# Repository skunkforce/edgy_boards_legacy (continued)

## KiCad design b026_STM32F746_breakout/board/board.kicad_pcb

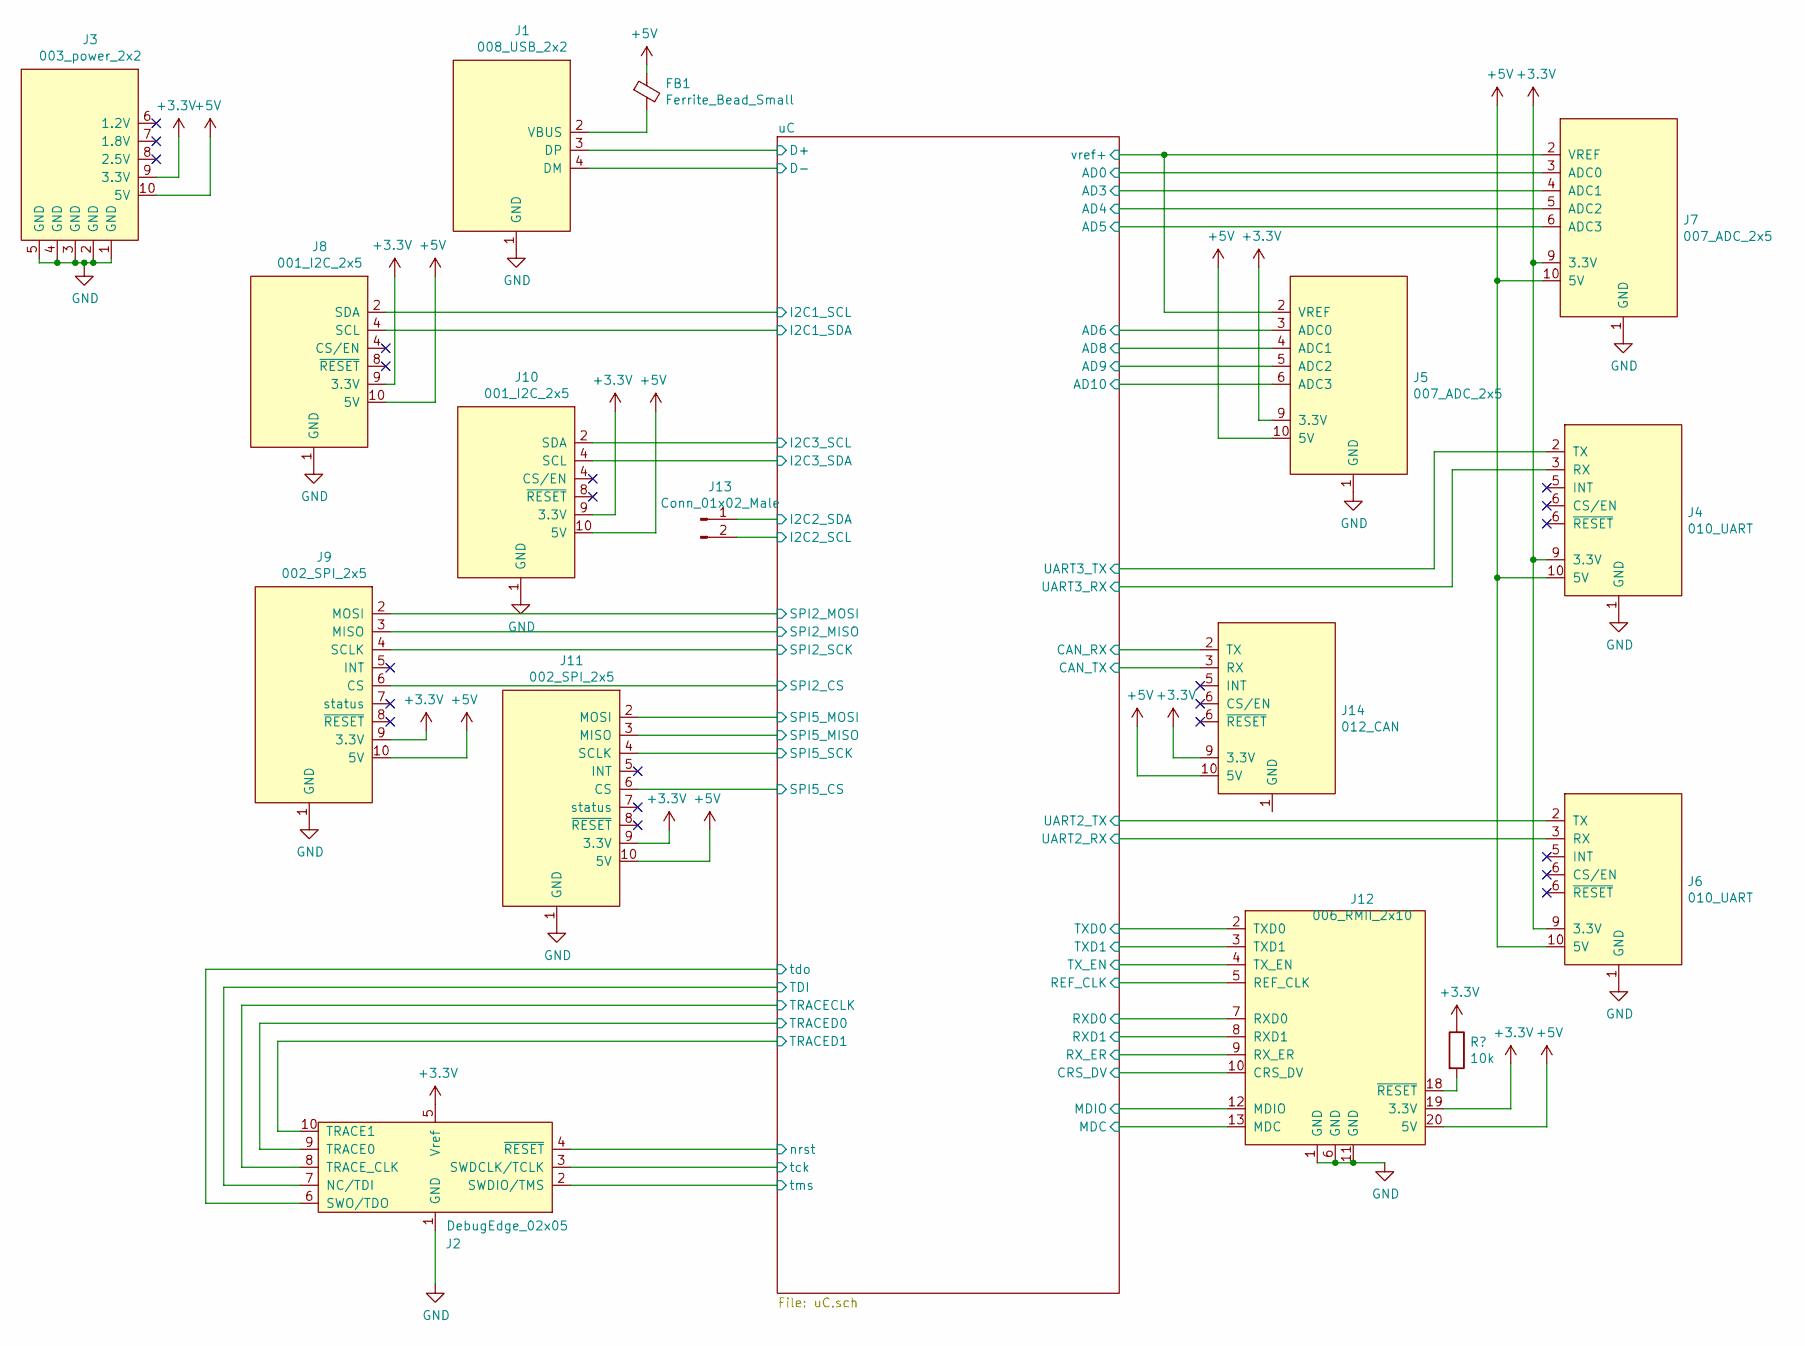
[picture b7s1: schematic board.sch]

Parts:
FB1: Ferrite_Bead_Small; L_0805_2012Metric
J1: 008_USB_2x2; on_edge_2x05_device
J2: DebugEdge_02x05; on_edge_2x05_device
J3: 003_power_2x2; on_edge_2x05_device
J4: 010_UART; on_edge_2x05_device
J5, J7: 007_ADC_2x5; on_edge_2x05_host
J6: 010_UART; on_edge_2x05_up_host
J8, J10: 001_I2C_2x5; on_edge_2x05_up_host
J9, J11: 002_SPI_2x5; on_edge_2x05_up_host
J12: 006_RMII_2x10; on_edge_2x10_host
J13: Conn_01x02_Male; PinHeader_1x02_P2.00mm_Vertical
J14: 012_CAN; on_edge_2x05_up_host

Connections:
+5V: FB1.1, J3.10 (5V), J4.10 (5V), J5.10 (5V), J6.10 (5V), J7.10 (5V), J8.10 (5V), J9.10 (5V), J10.10 (5V), J11.10 (5V), J12.20 (5V), J14.10 (5V)
/uC/AD0: J7.3 (ADC0); also elsewhere on the board
/uC/AD3: J7.4 (ADC1); also elsewhere on the board
/uC/AD4: J7.5 (ADC2); also elsewhere on the board
/uC/AD5: J7.6 (ADC3); also elsewhere on the board
/uC/AD6: J5.3 (ADC0); also elsewhere on the board
/uC/AD8: J5.4 (ADC1); also elsewhere on the board
/uC/AD9: J5.5 (ADC2); also elsewhere on the board
/uC/AD10: J5.6 (ADC3); also elsewhere on the board
/uC/CAN_RX: J14.2 (TX); also elsewhere on the board
/uC/CAN_TX: J14.3 (RX); also elsewhere on the board
/uC/CRS_DV: J12.10 (CRS_DV); also elsewhere on the board
/uC/D+: J1.3 (DP); also elsewhere on the board
/uC/D-: J1.4 (DM); also elsewhere on the board
/uC/I2C1_SCL: J8.2 (SDA); also elsewhere on the board
/uC/I2C2_SCL: J13.2; also elsewhere on the board
/uC/I2C2_SDA: J13.1; also elsewhere on the board
/uC/I2C3_SCL: J10.2 (SDA); also elsewhere on the board
/uC/MDC: J12.13 (MDC); also elsewhere on the board
/uC/MDIO: J12.12 (MDIO); also elsewhere on the board
/uC/REF_CLK: J12.5 (REF_CLK); also elsewhere on the board
/uC/RXD0: J12.7 (RXD0); also elsewhere on the board
/uC/RXD1: J12.8 (RXD1); also elsewhere on the board
/uC/RX_ER: J12.9 (RX_ER); also elsewhere on the board
/uC/SPI2_CS: J9.6 (CS); also elsewhere on the board
/uC/SPI2_MISO: J9.3 (MISO); also elsewhere on the board
/uC/SPI2_MOSI: J9.2 (MOSI); also elsewhere on the board
/uC/SPI2_SCK: J9.4 (SCLK); also elsewhere on the board
/uC/SPI5_CS: J11.6 (CS); also elsewhere on the board
/uC/SPI5_MISO: J11.3 (MISO); also elsewhere on the board
/uC/SPI5_MOSI: J11.2 (MOSI); also elsewhere on the board
/uC/SPI5_SCK: J11.4 (SCLK); also elsewhere on the board
/uC/TDI: J2.7 (NC/TDI); also elsewhere on the board
/uC/TRACECLK: J2.8 (TRACE_CLK); also elsewhere on the board
/uC/TRACED0: J2.9 (TRACE0); also elsewhere on the board
/uC/TRACED1: J2.10 (TRACE1); also elsewhere on the board
/uC/TXD0: J12.2 (TXD0); also elsewhere on the board
/uC/TXD1: J12.3 (TXD1); also elsewhere on the board
/uC/TX_EN: J12.4 (TX_EN); also elsewhere on the board
/uC/UART2_RX: J6.3 (RX); also elsewhere on the board
/uC/UART2_TX: J6.2 (TX); also elsewhere on the board
/uC/UART3_RX: J4.3 (RX); also elsewhere on the board
/uC/UART3_TX: J4.2 (TX); also elsewhere on the board
/uC/nrst: J2.4 (~RESET~); also elsewhere on the board
/uC/tck: J2.3 (SWDCLK/TCLK); also elsewhere on the board
/uC/tdo: J2.6 (SWO/TDO); also elsewhere on the board
/uC/tms: J2.2 (SWDIO/TMS); also elsewhere on the board
/uC/vref+: J5.2 (VREF), J7.2 (VREF); also elsewhere on the board
GND: J1.1 (GND), J2.1 (GND), J3.1 (GND), J3.2 (GND), J3.3 (GND), J3.4 (GND), J3.5 (GND), J4.1 (GND), J5.1 (GND), J6.1 (GND), J7.1 (GND), J8.1 (GND), J9.1 (GND), J10.1 (GND), J11.1 (GND), J12.1 (GND), J12.6 (GND), J12.11 (GND); also elsewhere on the board
unnamed: FB1.2, J1.2 (VBUS)
unnamed 57: J12.18 (~RESET); also elsewhere on the board

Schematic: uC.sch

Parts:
C1, C4, C9, C10, C12, C36, C37, C40, C42, C44, C45, C47: 100nF; C_0603_1608Metric
C8, C16, C17, C41, C43: 1uF; C_0603_1608Metric
C19, C20: 2.2uF; C_0603_1608Metric_Pad1.05x0.95mm_HandSolder
C21, C22: 22pF; C_0603_1608Metric_Pad1.05x0.95mm_HandSolder
C23, C24: 10pF; C_0603_1608Metric_Pad1.05x0.95mm_HandSolder
FB2, FB3: FCM1608KF-601T03 TypeA; L_0805_2012Metric
R4, R5, R7, R8: 10k; R_0603_1608Metric_Pad1.05x0.95mm_HandSolder
U1: STM32F767ZITx; LQFP-144_20x20mm_P0.5mm
Y1: Crystal 32kHz; Crystal_SMD_3215-2Pin_3.2x1.5mm; Digi-Key_PN 644-1156-1-ND
Y2: Crystal_GND24; Crystal_SMD_Abracon_ABM8G-4Pin_3.2x2.5mm; Digi-Key_PN 535-9140-1-ND

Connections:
/uC/AD0: U1.34 (PA0); also elsewhere on the board
/uC/AD3: U1.37 (PA3); also elsewhere on the board
/uC/AD4: U1.40 (PA4); also elsewhere on the board
/uC/AD5: U1.41 (PA5); also elsewhere on the board
/uC/AD6: U1.42 (PA6); also elsewhere on the board
/uC/AD8: U1.46 (PB0); also elsewhere on the board
/uC/AD9: U1.47 (PB1); also elsewhere on the board
/uC/AD10: U1.26 (PC0); also elsewhere on the board
/uC/CAN_RX: U1.114 (PD0); also elsewhere on the board
/uC/CAN_TX: U1.115 (PD1); also elsewhere on the board
/uC/CRS_DV: U1.43 (PA7); also elsewhere on the board
/uC/D+: U1.104 (PA12); also elsewhere on the board
/uC/D-: U1.103 (PA11); also elsewhere on the board
/uC/GNDA: C16.2, C17.2, FB2.1, U1.31 (VSSA)
/uC/I2C1_SCL: U1.136 (PB6); also elsewhere on the board
/uC/I2C2_SCL: U1.11 (PF1); also elsewhere on the board
/uC/I2C2_SDA: U1.10 (PF0); also elsewhere on the board
/uC/I2C3_SCL: U1.100 (PA8); also elsewhere on the board
/uC/MDC: U1.27 (PC1); also elsewhere on the board
/uC/MDIO: U1.36 (PA2); also elsewhere on the board
/uC/REF_CLK: U1.35 (PA1); also elsewhere on the board
/uC/RXD0: U1.44 (PC4); also elsewhere on the board
/uC/RXD1: U1.45 (PC5); also elsewhere on the board
/uC/RX_ER: R8.2; also elsewhere on the board
/uC/SPI2_CS: U1.73 (PB12); also elsewhere on the board
/uC/SPI2_MISO: U1.28 (PC2); also elsewhere on the board
/uC/SPI2_MOSI: U1.29 (PC3); also elsewhere on the board
/uC/SPI2_SCK: U1.69 (PB10); also elsewhere on the board
/uC/SPI5_CS: U1.18 (PF6); also elsewhere on the board
/uC/SPI5_MISO: U1.20 (PF8); also elsewhere on the board
/uC/SPI5_MOSI: U1.21 (PF9); also elsewhere on the board
/uC/SPI5_SCK: U1.19 (PF7); also elsewhere on the board
/uC/TDI: U1.110 (PA15); also elsewhere on the board
/uC/TRACECLK: U1.1 (PE2); also elsewhere on the board
/uC/TRACED0: U1.142 (PE1); also elsewhere on the board
/uC/TRACED1: U1.141 (PE0); also elsewhere on the board
/uC/TXD0: U1.128 (PG13); also elsewhere on the board
/uC/TXD1: U1.74 (PB13); also elsewhere on the board
/uC/TX_EN: U1.126 (PG11); also elsewhere on the board
/uC/UART2_RX: U1.122 (PD6); also elsewhere on the board
/uC/UART2_TX: U1.119 (PD5); also elsewhere on the board
/uC/UART3_RX: U1.78 (PD9); also elsewhere on the board
/uC/UART3_TX: U1.77 (PD8); also elsewhere on the board
/uC/nrst: R5.1, U1.25 (NRST); also elsewhere on the board
/uC/tck: U1.109 (PA14); also elsewhere on the board
/uC/tdo: U1.133 (PB3); also elsewhere on the board
/uC/tms: U1.105 (PA13); also elsewhere on the board
/uC/vref+: C16.1, C17.1, FB3.1, U1.32 (VREF+), U1.33 (VDDA); also elsewhere on the board
GND: C1.2, C4.2, C8.2, C9.2, C10.2, C12.2, C19.2, C20.2, C21.2, C22.2, C23.2, C24.2, C36.2, C37.2, C40.2, C41.2, C42.2, C43.2, C44.2, C45.2, C47.2, FB2.2, R7.1, R8.1, U1.16 (VSS), U1.38 (VSS), U1.51 (VSS), U1.61 (VSS), U1.83 (VSS), U1.94 (VSS), U1.107 (VSS), U1.120 (VSS), U1.130 (VSS), Y2.2, Y2.4; also elsewhere on the board
unnamed: C19.1, U1.71 (VCAP_1)
unnamed: C20.1, U1.106 (VCAP_2)
unnamed: C21.1, U1.23 (PH0), Y2.3
unnamed: C22.1, U1.24 (PH1), Y2.1
unnamed: C23.1, U1.8 (PC14), Y1.2
unnamed: C24.1, U1.9 (PC15), Y1.1
unnamed: R4.1, U1.143 (PDR_ON)
unnamed: R7.2, U1.138 (BOOT0)

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
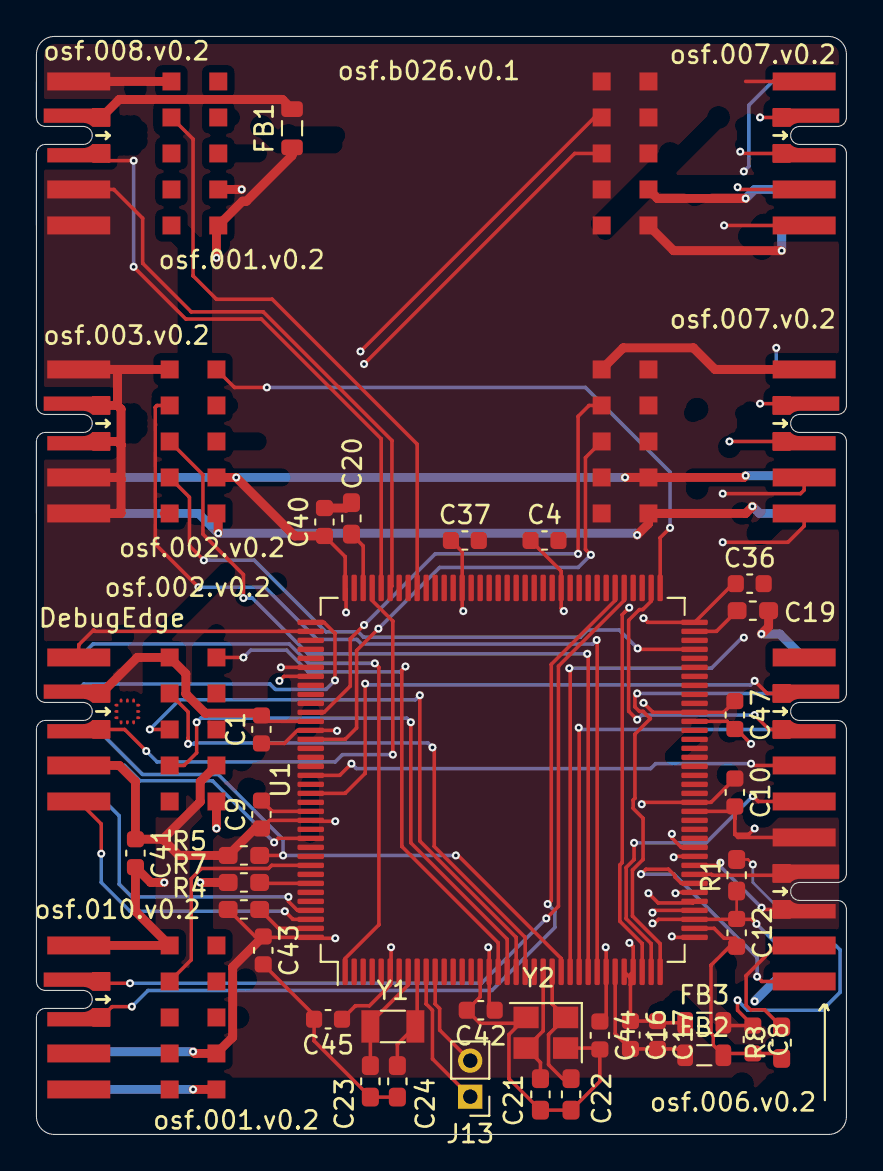
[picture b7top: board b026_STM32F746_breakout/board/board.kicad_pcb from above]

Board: 4 copper layers, 45.0 x 61.0 mm, 48 parts (0 on the bottom side), 61 nets.

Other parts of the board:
R1: 10k; R_0603_1608Metric_Pad1.05x0.95mm_HandSolder

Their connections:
unnamed 57: R1.2; also elsewhere on the board
